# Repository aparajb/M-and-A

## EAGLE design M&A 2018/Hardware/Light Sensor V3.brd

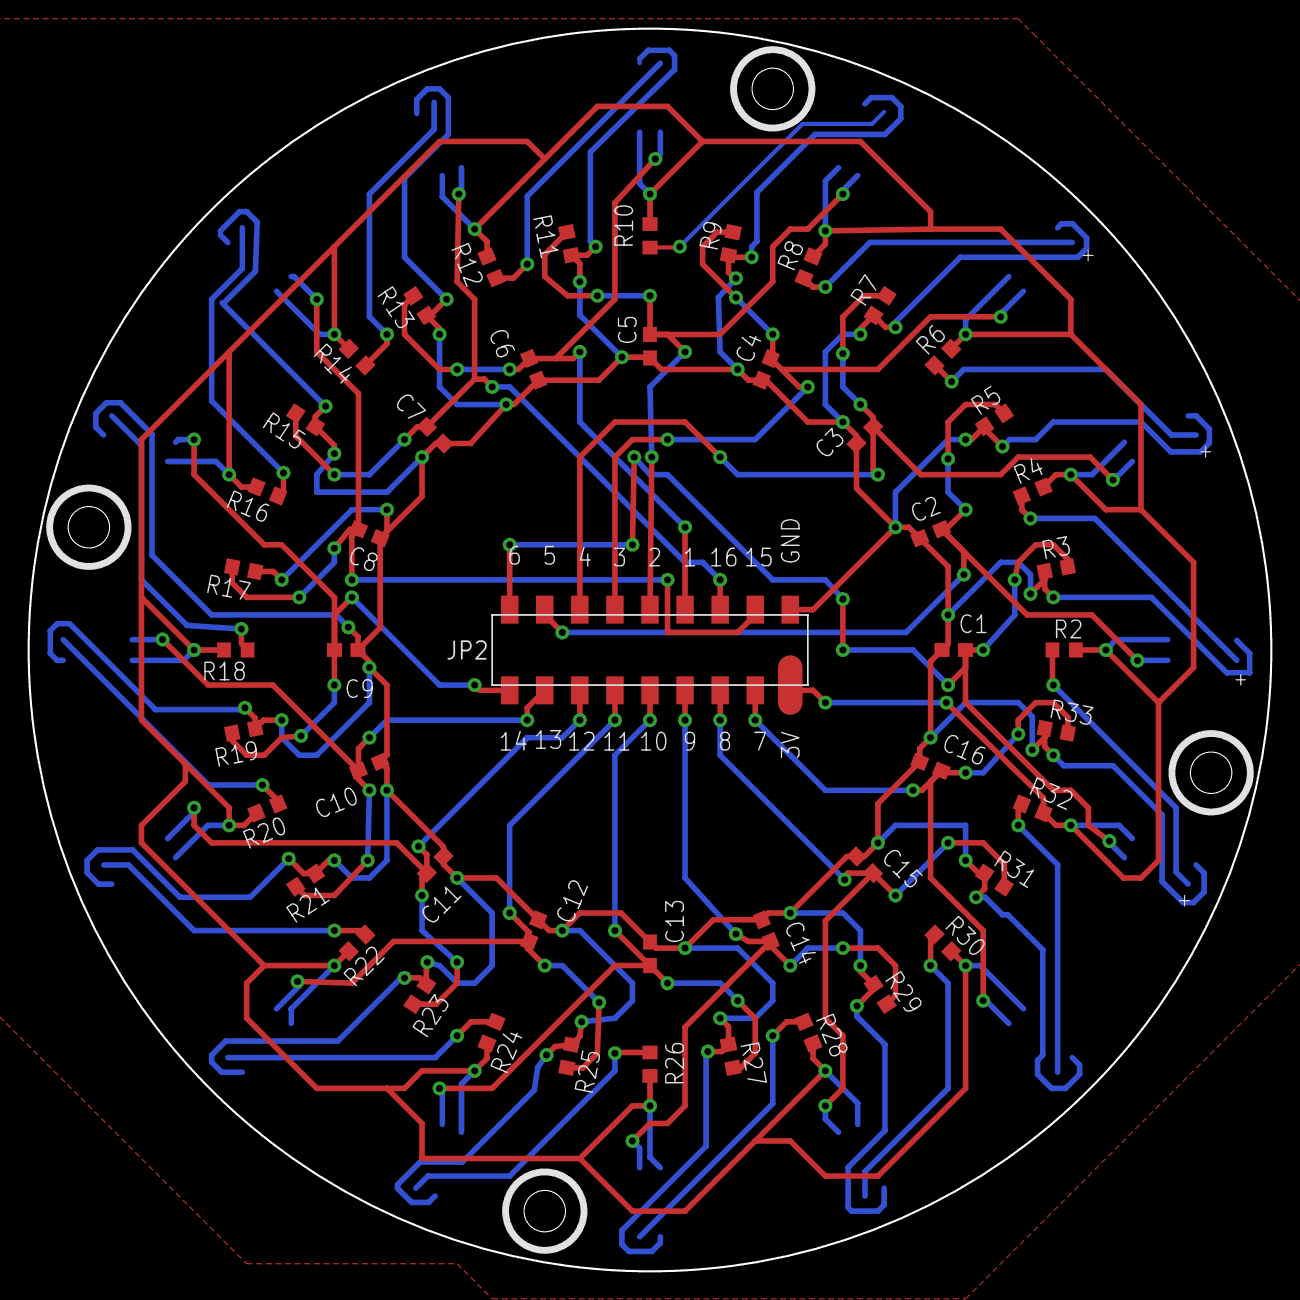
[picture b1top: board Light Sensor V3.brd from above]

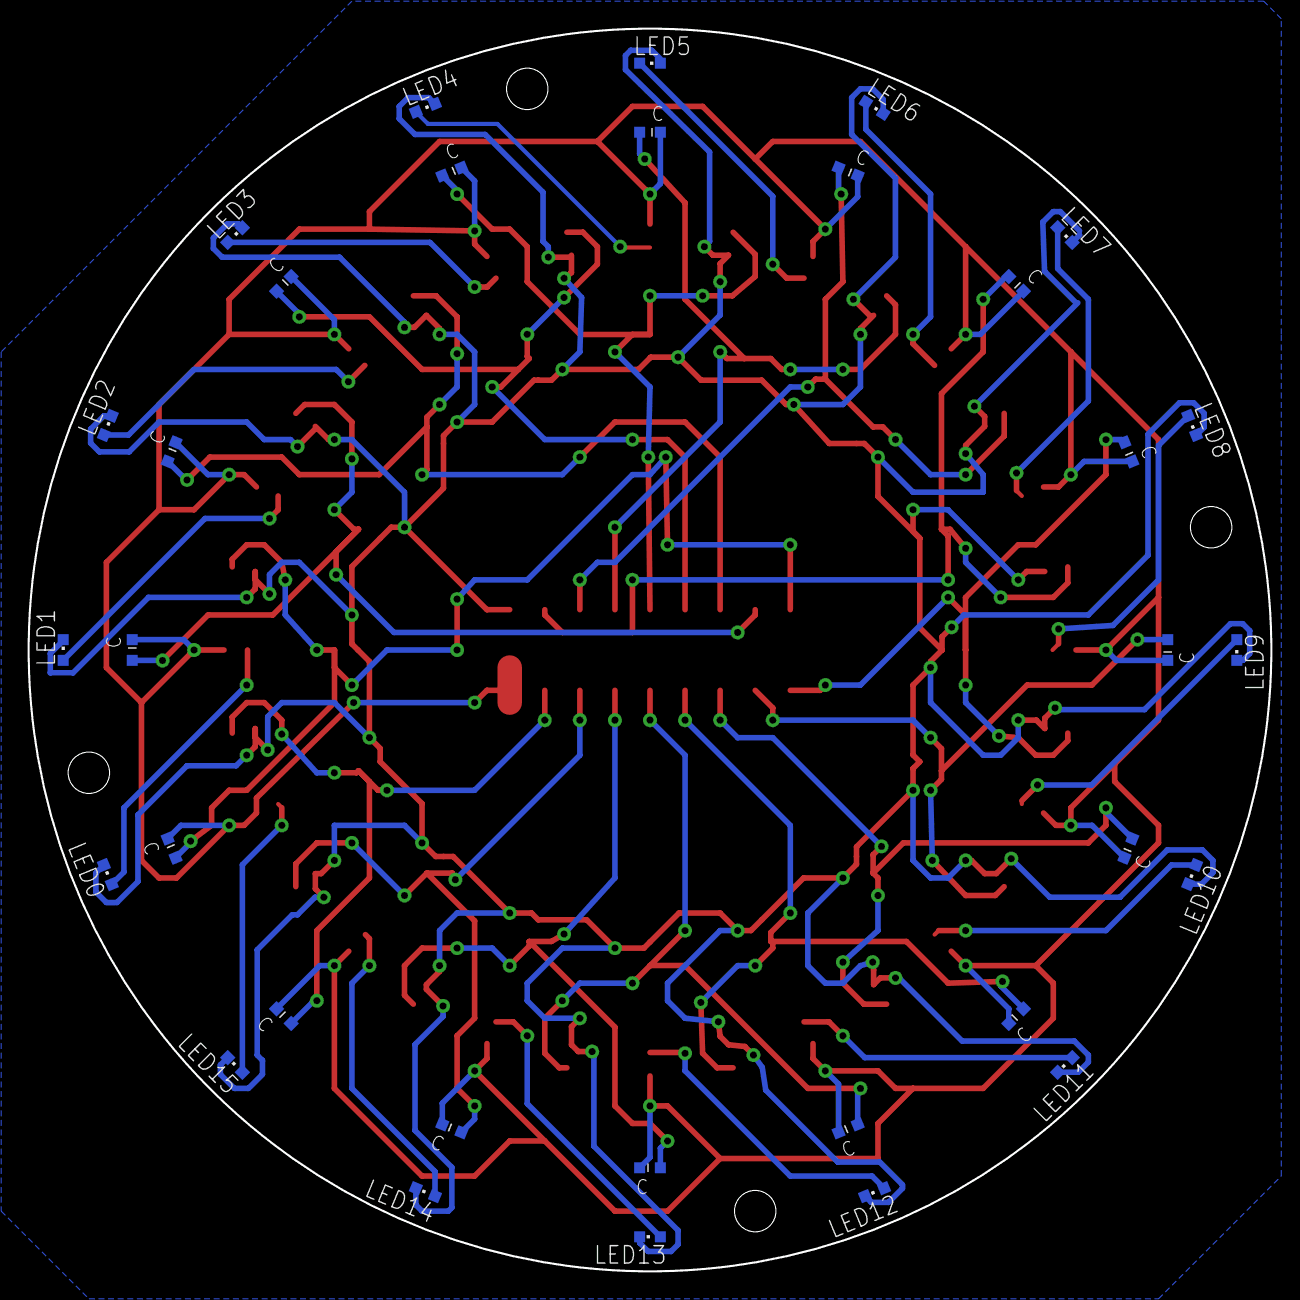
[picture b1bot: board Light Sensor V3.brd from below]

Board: 2 copper layers, 90.0 x 90.0 mm, 81 parts (32 on the bottom side), 34 nets.

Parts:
C1, C2, C3, C4, C5, C6, C7, C8, C9, C10, C11, C12, C13, C14, C15, C16: 0.1uF; C0603
JP2: 2X09_SMT
LED0, LED1, LED2, LED3, LED4, LED5, LED6, LED7, LED8, LED9, LED10, LED11, LED12, LED13, LED14, LED15: CHIPLED_0603
LS0, LS1, LS2, LS3, LS4, LS5, LS6, LS7, LS8, LS9, LS10, LS11, LS12, LS13, LS14, LS15: ALS; SMD
R2, R4, R6, R8, R10, R12, R14, R16, R18, R20, R22, R24, R26, R28, R30, R32: 100; R0603
R3, R5, R7, R9, R11, R13, R15, R17, R19, R21, R23, R25, R27, R29, R31, R33: 33K; R0603

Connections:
+3V3: JP2.17, LS0.C, LS1.C, LS2.C, LS3.C, LS4.C, LS5.C, LS6.C, LS7.C, LS8.C, LS9.C, LS10.C, LS11.C, LS12.C, LS13.C, LS14.C, LS15.C, R2.2, R4.2, R6.2, R8.2, R10.2, R12.2, R14.2, R16.2, R18.2, R20.2, R22.2, R24.2, R26.2, R28.2, R30.2, R32.2
GND: C1.1, C2.1, C3.1, C4.1, C5.1, C6.1, C7.1, C8.1, C9.1, C10.1, C11.1, C12.1, C13.1, C14.1, C15.1, C16.1, JP2.18, LED0.C, LED1.C, LED2.C, LED3.C, LED4.C, LED5.C, LED6.C, LED7.C, LED8.C, LED9.C, LED10.C, LED11.C, LED12.C, LED13.C, LED14.C, LED15.C, R3.1, R5.1, R7.1, R9.1, R11.1, R13.1, R15.1, R17.1, R19.1, R21.1, R23.1, R25.1, R27.1, R29.1, R31.1, R33.1
LS0: C1.2, JP2.2, LS0.E, R3.2
LS1: C2.2, JP2.4, LS1.E, R5.2
LS2: C3.2, JP2.6, LS2.E, R7.2
LS3: C4.2, JP2.8, LS3.E, R9.2
LS4: C5.2, JP2.10, LS4.E, R11.2
LS5: C6.2, JP2.12, LS5.E, R13.2
LS6: C7.2, JP2.14, LS6.E, R15.2
LS7: C8.2, JP2.16, LS7.E, R17.2
LS8: C9.2, JP2.1, LS8.E, R19.2
LS9: C10.2, JP2.3, LS9.E, R21.2
LS10: C11.2, JP2.5, LS10.E, R23.2
LS11: C12.2, JP2.7, LS11.E, R25.2
LS12: C13.2, JP2.9, LS12.E, R27.2
LS13: C14.2, JP2.11, LS13.E, R29.2
LS14: C15.2, JP2.13, LS14.E, R31.2
LS15: C16.2, JP2.15, LS15.E, R33.2
unnamed: LED0.A, R2.1
unnamed: LED1.A, R4.1
unnamed: LED2.A, R6.1
unnamed: LED3.A, R8.1
unnamed: LED4.A, R10.1
unnamed: LED5.A, R12.1
unnamed: LED6.A, R14.1
unnamed: LED7.A, R16.1
unnamed: LED8.A, R18.1
unnamed: LED9.A, R20.1
unnamed: LED10.A, R22.1
unnamed: LED11.A, R24.1
unnamed: LED12.A, R26.1
unnamed: LED13.A, R28.1
unnamed: LED14.A, R30.1
unnamed: LED15.A, R32.1

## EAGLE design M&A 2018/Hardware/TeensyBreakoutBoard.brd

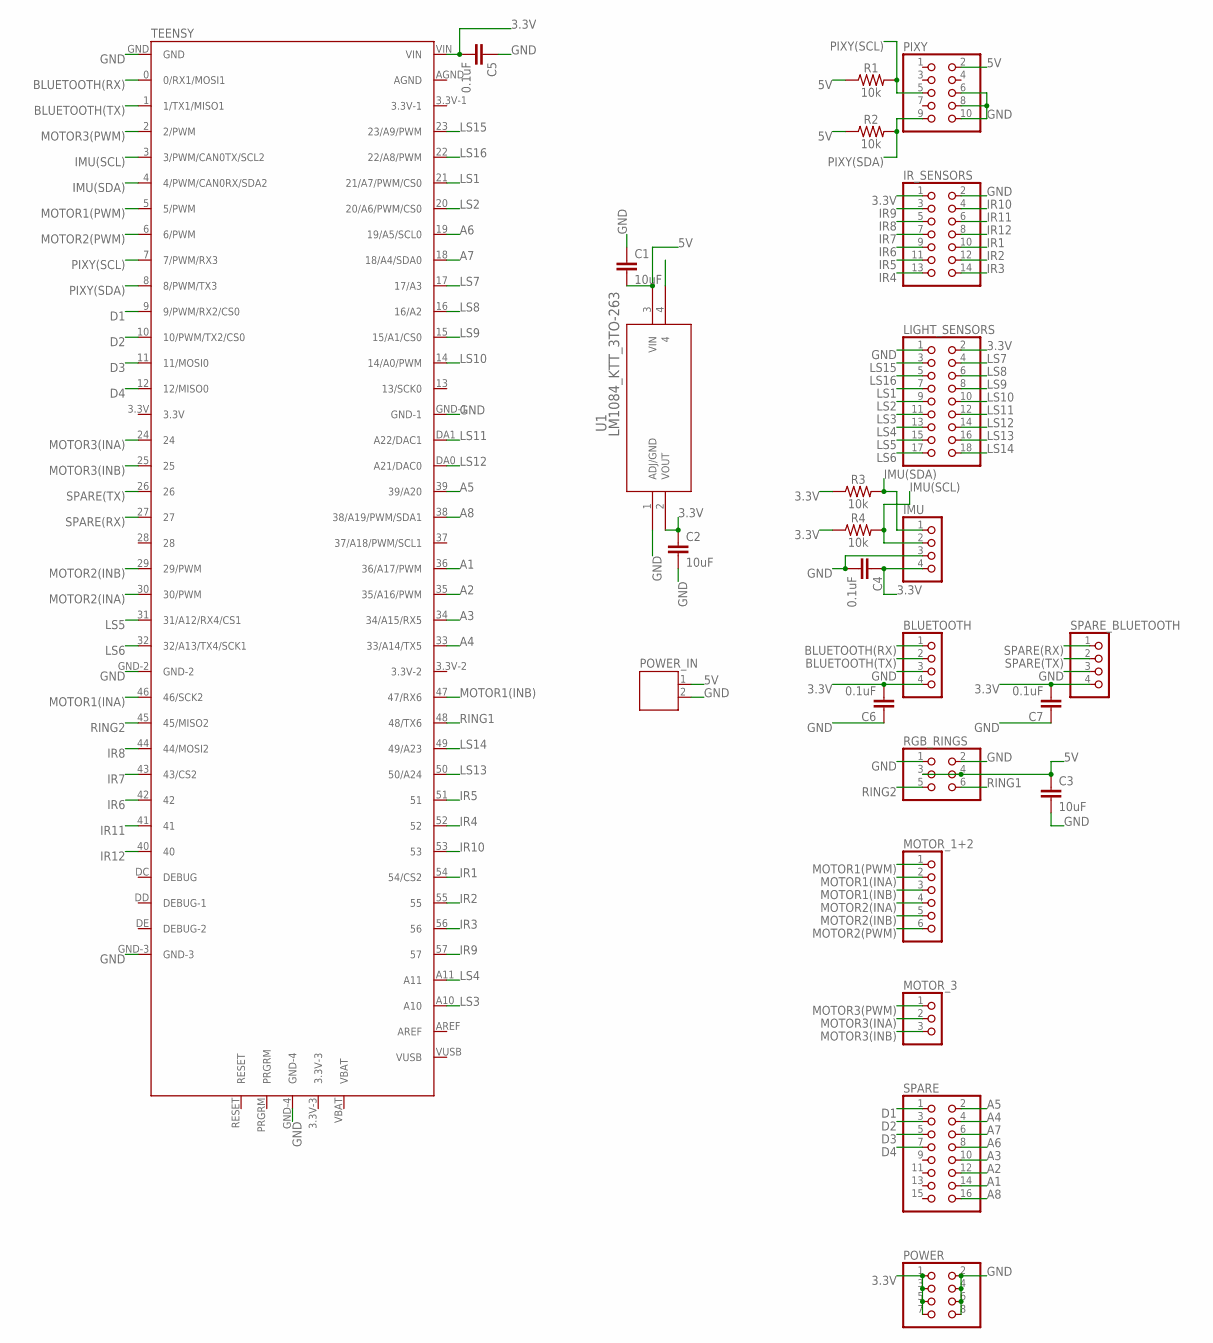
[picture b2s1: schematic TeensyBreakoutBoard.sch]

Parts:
BLUETOOTH: PINHD-1X4; 1X04
C1, C2, C3: 10uF; 0805
C4, C5, C6, C7: 0.1uF; 0603
IMU: PINHD-1X4; 1X04
IR_SENSORS: PINHD-2X7; 2X07
LIGHT_SENSORS: PINHD-2X9; 2X09
MOTOR_1+2: PINHD-1X6; 1X06
MOTOR_3: PINHD-1X3; 1X03
PIXY: PINHD-2X5; 2X05
POWER: PINHD-2X4; 2X04
POWER_IN: JST-PH2
R1, R2, R3, R4: 10k; 0603
RGB_RINGS: PINHD-2X3; 2X03
SPARE: PINHD-2X8; 2X08
SPARE_BLUETOOTH: PINHD-1X4; 1X04
TEENSY: TEENSY-3.5
U1: LM1084_KTT_3TO-263; TS3B

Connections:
3.3V: BLUETOOTH.4, C2.1, C4.1, C5.2, C6.2, C7.2, IMU.4, IR_SENSORS.1, LIGHT_SENSORS.2, POWER.1, POWER.3, POWER.5, POWER.7, R3.1, R4.1, SPARE_BLUETOOTH.4, TEENSY.VIN, U1.2 (VOUT)
5V: C1.2, C3.1, PIXY.2, POWER_IN.1, R1.1, R2.1, RGB_RINGS.3, RGB_RINGS.4, U1.3 (VIN)
A1: SPARE.14, TEENSY.36 (36/A17/PWM)
A2: SPARE.12, TEENSY.35 (35/A16/PWM)
A3: SPARE.10, TEENSY.34 (34/A15/RX5)
A4: SPARE.4, TEENSY.33 (33/A14/TX5)
A5: SPARE.2, TEENSY.39 (39/A20)
A6: SPARE.8, TEENSY.19 (19/A5/SCL0)
A7: SPARE.6, TEENSY.18 (18/A4/SDA0)
A8: SPARE.16, TEENSY.38 (38/A19/PWM/SDA1)
BLUETOOTH(RX): BLUETOOTH.1, TEENSY.0 (0/RX1/MOSI1)
BLUETOOTH(TX): BLUETOOTH.2, TEENSY.1 (1/TX1/MISO1)
D1: SPARE.1, TEENSY.9 (9/PWM/RX2/CS0)
D2: SPARE.3, TEENSY.10 (10/PWM/TX2/CS0)
D3: SPARE.5, TEENSY.11 (11/MOSI0)
D4: SPARE.7, TEENSY.12 (12/MISO0)
GND: BLUETOOTH.3, C1.1, C2.2, C3.2, C4.2, C5.1, C6.1, C7.1, IMU.3, IR_SENSORS.2, LIGHT_SENSORS.1, PIXY.6, PIXY.8, PIXY.10, POWER.2, POWER.4, POWER.6, POWER.8, POWER_IN.2, RGB_RINGS.1, RGB_RINGS.2, SPARE_BLUETOOTH.3, TEENSY.GND, TEENSY.GND-1, TEENSY.GND-2, TEENSY.GND-3, TEENSY.GND-4, U1.1 (ADJ/GND)
IMU(SCL): IMU.2, R4.2, TEENSY.3 (3/PWM/CAN0TX/SCL2)
IMU(SDA): IMU.1, R3.2, TEENSY.4 (4/PWM/CAN0RX/SDA2)
IR1: IR_SENSORS.10, TEENSY.54 (54/CS2)
IR2: IR_SENSORS.12, TEENSY.55
IR3: IR_SENSORS.14, TEENSY.56
IR4: IR_SENSORS.13, TEENSY.52
IR5: IR_SENSORS.11, TEENSY.51
IR6: IR_SENSORS.9, TEENSY.42
IR7: IR_SENSORS.7, TEENSY.43 (43/CS2)
IR8: IR_SENSORS.5, TEENSY.44 (44/MOSI2)
IR9: IR_SENSORS.3, TEENSY.57
IR10: IR_SENSORS.4, TEENSY.53
IR11: IR_SENSORS.6, TEENSY.41
IR12: IR_SENSORS.8, TEENSY.40
LS1: LIGHT_SENSORS.7, TEENSY.21 (21/A7/PWM/CS0)
LS2: LIGHT_SENSORS.9, TEENSY.20 (20/A6/PWM/CS0)
LS3: LIGHT_SENSORS.11, TEENSY.A10
LS4: LIGHT_SENSORS.13, TEENSY.A11
LS5: LIGHT_SENSORS.15, TEENSY.31 (31/A12/RX4/CS1)
LS6: LIGHT_SENSORS.17, TEENSY.32 (32/A13/TX4/SCK1)
LS7: LIGHT_SENSORS.4, TEENSY.17 (17/A3)
LS8: LIGHT_SENSORS.6, TEENSY.16 (16/A2)
LS9: LIGHT_SENSORS.8, TEENSY.15 (15/A1/CS0)
LS10: LIGHT_SENSORS.10, TEENSY.14 (14/A0/PWM)
LS11: LIGHT_SENSORS.12, TEENSY.DA1 (A22/DAC1)
LS12: LIGHT_SENSORS.14, TEENSY.DA0 (A21/DAC0)
LS13: LIGHT_SENSORS.16, TEENSY.50 (50/A24)
LS14: LIGHT_SENSORS.18, TEENSY.49 (49/A23)
LS15: LIGHT_SENSORS.3, TEENSY.23 (23/A9/PWM)
LS16: LIGHT_SENSORS.5, TEENSY.22 (22/A8/PWM)
MOTOR1(INA): MOTOR_1+2.2, TEENSY.46 (46/SCK2)
MOTOR1(INB): MOTOR_1+2.3, TEENSY.47 (47/RX6)
MOTOR1(PWM): MOTOR_1+2.1, TEENSY.5 (5/PWM)
MOTOR2(INA): MOTOR_1+2.4, TEENSY.30 (30/PWM)
MOTOR2(INB): MOTOR_1+2.5, TEENSY.29 (29/PWM)
MOTOR2(PWM): MOTOR_1+2.6, TEENSY.6 (6/PWM)
MOTOR3(INA): MOTOR_3.2, TEENSY.24
MOTOR3(INB): MOTOR_3.3, TEENSY.25
MOTOR3(PWM): MOTOR_3.1, TEENSY.2 (2/PWM)
PIXY(SCL): PIXY.5, R1.2, TEENSY.7 (7/PWM/RX3)
PIXY(SDA): PIXY.9, R2.2, TEENSY.8 (8/PWM/TX3)
RING1: RGB_RINGS.6, TEENSY.48 (48/TX6)
RING2: RGB_RINGS.5, TEENSY.45 (45/MISO2)
SPARE(RX): SPARE_BLUETOOTH.1, TEENSY.27
SPARE(TX): SPARE_BLUETOOTH.2, TEENSY.26

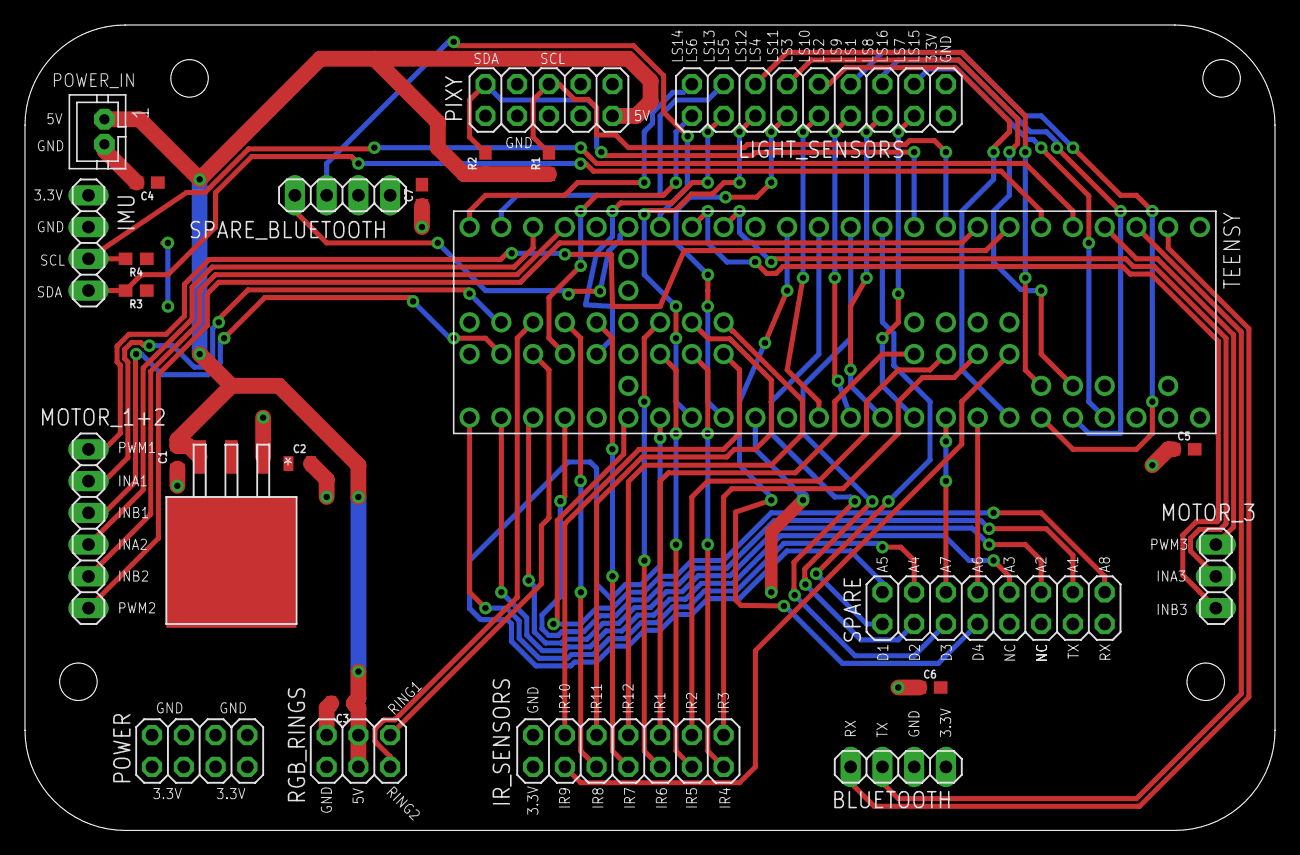
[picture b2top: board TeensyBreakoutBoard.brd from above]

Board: 2 copper layers, 100.0 x 64.4 mm, 25 parts (0 on the bottom side), 62 nets.

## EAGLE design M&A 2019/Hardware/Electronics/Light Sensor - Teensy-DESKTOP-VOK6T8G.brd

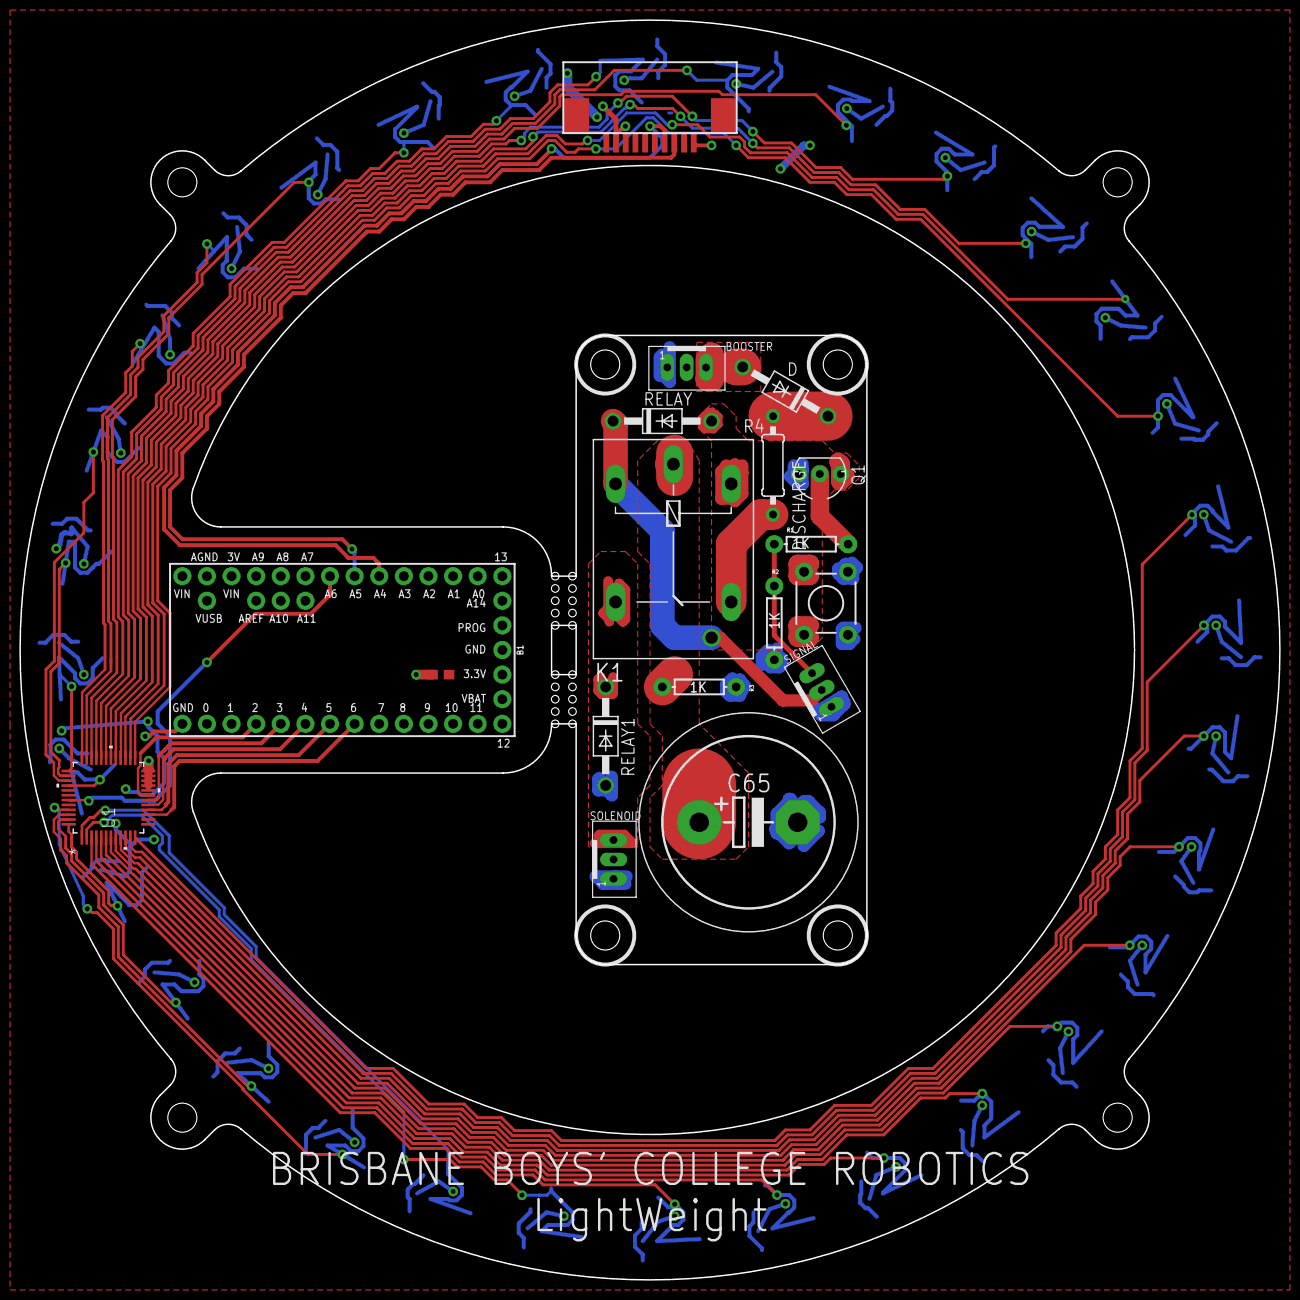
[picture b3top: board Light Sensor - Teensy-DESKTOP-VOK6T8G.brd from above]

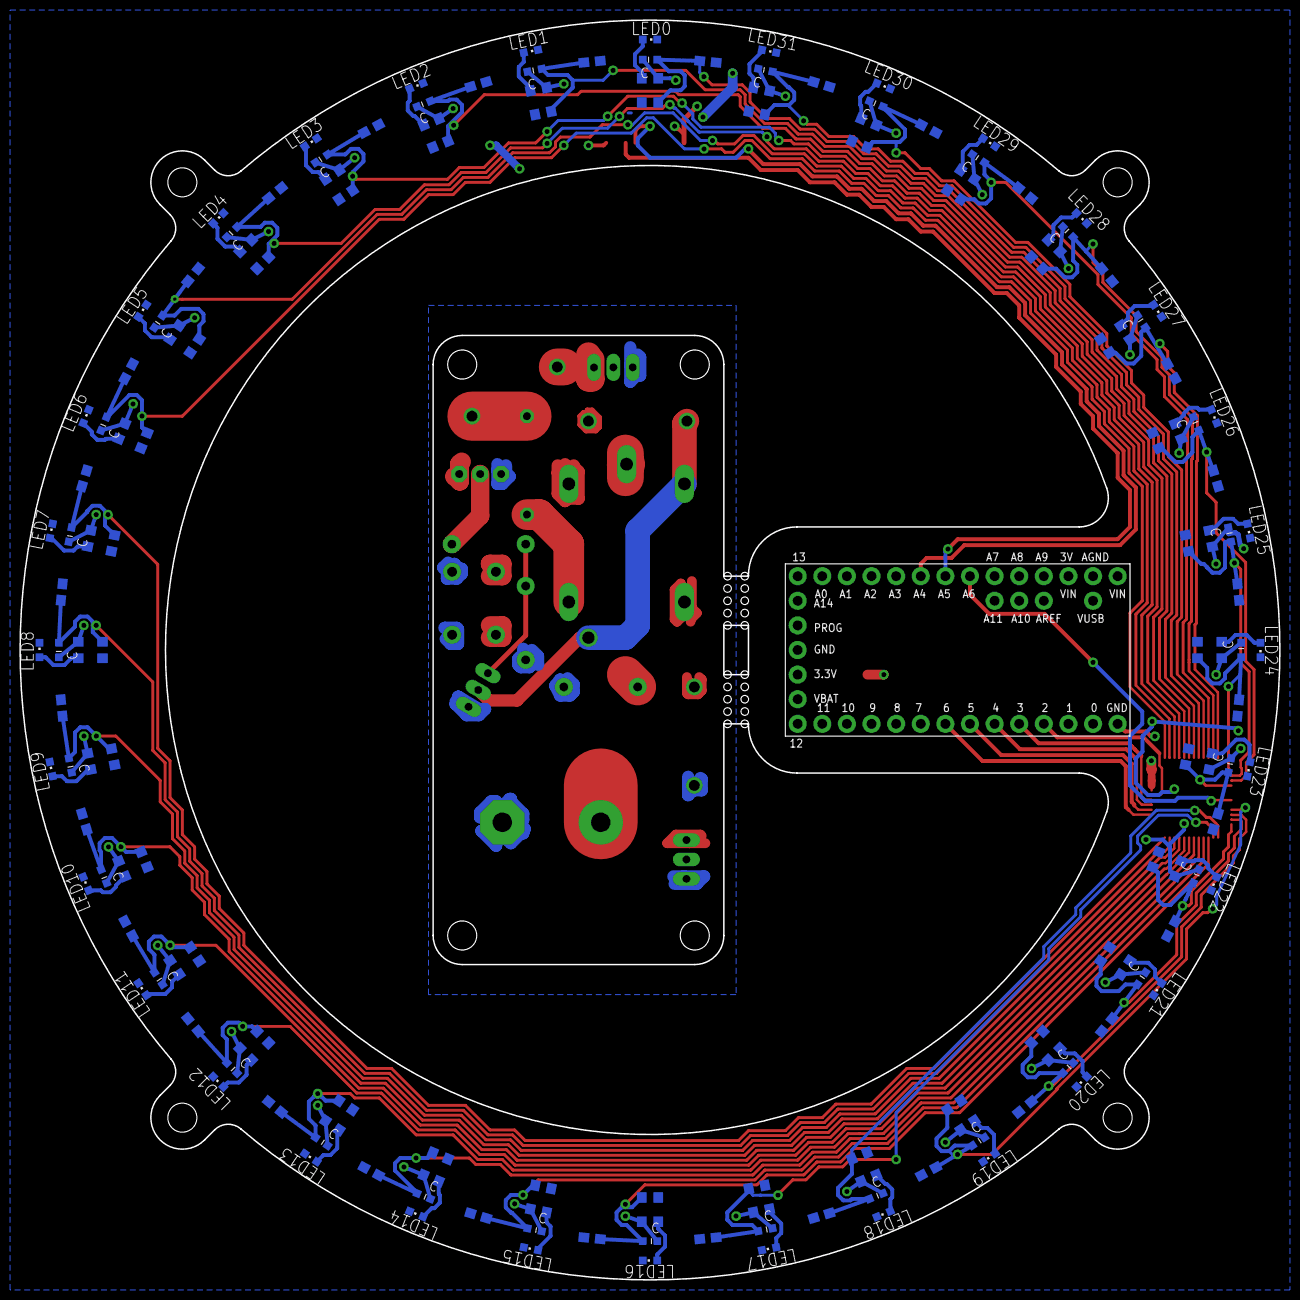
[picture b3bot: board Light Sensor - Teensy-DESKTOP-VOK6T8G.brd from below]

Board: 2 copper layers, 130.0 x 130.0 mm, 178 parts (160 on the bottom side), 83 nets.

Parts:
B1: TEENSY-3.1SILK; TEENSY-3.1
BOOSTER: JST-PH_3-PIN_HEADER; JST_B3B-PH_HEADER
C1, C2, C3, C4, C5, C6, C7, C8, C9, C10, C11, C12, C13, C14, C15, C16, C17, C18, C19, C20, C21, C22, C23, C24, C25, C26, C27, C28, C29, C30, C31, C32: 0.1uF; C0603
C33: 0.1uF; 0603
C65: 3300uF; EB22,5D
D: 1N4004; DO41-10
DISCHARGE: TACTILE-PTH
K1: G5LE
LED0, LED1, LED2, LED3, LED4, LED5, LED6, LED7, LED8, LED9, LED10, LED11, LED12, LED13, LED14, LED15, LED16, LED17, LED18, LED19, LED20, LED21, LED22, LED23, LED24, LED25, LED26, LED27, LED28, LED29, LED30, LED31: CHIPLED_0603
LS0, LS1, LS2, LS3, LS4, LS5, LS6, LS7, LS8, LS9, LS10, LS11, LS12, LS13, LS14, LS15, LS16, LS17, LS18, LS19, LS20, LS21, LS22, LS23, LS24, LS25, LS26, LS27, LS28, LS29, LS30, LS31: ALS; SMD
Q1: FQN1N50CI; TO92-INLINE
R1, R2, R3: 1K; AXIAL-0.3
R4: 50ohm; 0207/10
RELAY, RELAY1: 1N4004; DO41-10
RL1, RL2, RL3, RL4, RL5, RL6, RL7, RL8, RL9, RL10, RL11, RL12, RL13, RL14, RL15, RL16, RL17, RL18, RL19, RL20, RL21, RL22, RL23, RL24, RL25, RL26, RL27, RL28, RL29, RL30, RL31, RL32: 100; R0603
RS1, RS2, RS3, RS4, RS5, RS6, RS7, RS8, RS9, RS10, RS11, RS12, RS13, RS14, RS15, RS16, RS17, RS18, RS19, RS20, RS21, RS22, RS23, RS24, RS25, RS26, RS27, RS28, RS29, RS30, RS31, RS32: 33K; R0603
SIGNAL: JST-PH_3-PIN_HEADER; JST_B3B-PH_HEADER
SOLENOID: JST-PH_3-PIN_HEADER; JST_B3B-PH_HEADER
U1: ADG732BSUZ-REEL; SU_48
U$1: FPC10

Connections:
+3V3: B1.3.3V, C33.2, LS0.C, LS1.C, LS2.C, LS3.C, LS4.C, LS5.C, LS6.C, LS7.C, LS8.C, LS9.C, LS10.C, LS11.C, LS12.C, LS13.C, LS14.C, LS15.C, LS16.C, LS17.C, LS18.C, LS19.C, LS20.C, LS21.C, LS22.C, LS23.C, LS24.C, LS25.C, LS26.C, LS27.C, LS28.C, LS29.C, LS30.C, LS31.C, RL1.2, RL2.2, RL3.2, RL4.2, RL5.2, RL6.2, RL7.2, RL8.2, RL9.2, RL10.2, RL11.2, RL12.2, RL13.2, RL14.2, RL15.2, RL16.2, RL17.2, RL18.2, RL19.2, RL20.2, RL21.2, RL22.2, RL23.2, RL24.2, RL25.2, RL26.2, RL27.2, RL28.2, RL29.2, RL30.2, RL31.2, RL32.2, U1.13, U1.14, U$1.2, U$1.10
+12V: K1.1, RELAY.C, SIGNAL.P2
CHARGE: C65.+, K1.P, R3.P$2
CONTROL1: B1.2, U1.19
CONTROL2: B1.3, U1.18
CONTROL3: B1.4, U1.17
CONTROL4: B1.5, U1.16
CONTROL5: B1.6, U1.15
GND: B1.GND, B1.GND1, BOOSTER.P1, C1.1, C2.1, C3.1, C4.1, C5.1, C6.1, C7.1, C8.1, C9.1, C10.1, C11.1, C12.1, C13.1, C14.1, C15.1, C16.1, C17.1, C18.1, C19.1, C20.1, C21.1, C22.1, C23.1, C24.1, C25.1, C26.1, C27.1, C28.1, C29.1, C30.1, C31.1, C32.1, C33.1, C65.-, DISCHARGE.1, DISCHARGE.2, LED0.C, LED1.C, LED2.C, LED3.C, LED4.C, LED5.C, LED6.C, LED7.C, LED8.C, LED9.C, LED10.C, LED11.C, LED12.C, LED13.C, LED14.C, LED15.C, LED16.C, LED17.C, LED18.C, LED19.C, LED20.C, LED21.C, LED22.C, LED23.C, LED24.C, LED25.C, LED26.C, LED27.C, LED28.C, LED29.C, LED30.C, LED31.C, Q1.3, R2.P$1, R3.P$1, RELAY1.A, RS1.1, RS2.1, RS3.1, RS4.1, RS5.1, RS6.1, RS7.1, RS8.1, RS9.1, RS10.1, RS11.1, RS12.1, RS13.1, RS14.1, RS15.1, RS16.1, RS17.1, RS18.1, RS19.1, RS20.1, RS21.1, RS22.1, RS23.1, RS24.1, RS25.1, RS26.1, RS27.1, RS28.1, RS29.1, RS30.1, RS31.1, RS32.1, SIGNAL.P1, SOLENOID.P1, U1.20, U1.21, U1.22, U1.23, U1.24, U$1.1, U$1.9
LS0: C1.2, LS0.E, RS1.2, U1.31
LS1: C2.2, LS1.E, RS2.2, U1.30
LS2: C3.2, LS2.E, RS3.2, U1.29
LS3: C4.2, LS3.E, RS4.2, U1.28
LS4: C5.2, LS4.E, RS5.2, U1.27
LS5: C6.2, LS5.E, RS6.2, U1.26
LS6: C7.2, LS6.E, RS7.2, U1.25
LS7: C8.2, LS7.E, RS8.2, U1.12
LS8: C9.2, LS8.E, RS9.2, U1.11
LS9: C10.2, LS9.E, RS10.2, U1.10
LS10: C11.2, LS10.E, RS11.2, U1.9
LS11: C12.2, LS11.E, RS12.2, U1.8
LS12: C13.2, LS12.E, RS13.2, U1.7
LS13: C14.2, LS13.E, RS14.2, U1.6
LS14: C15.2, LS14.E, RS15.2, U1.5
LS15: C16.2, LS15.E, RS16.2, U1.4
LS16: C17.2, LS16.E, RS17.2, U1.3
LS17: C18.2, LS17.E, RS18.2, U1.2
LS18: C19.2, LS18.E, RS19.2, U1.1
LS19: C20.2, LS19.E, RS20.2, U1.45
LS20: C21.2, LS20.E, RS21.2, U1.46
LS21: C22.2, LS21.E, RS22.2, U1.47
LS22: C23.2, LS22.E, RS23.2, U1.48
LS23: C24.2, LS23.E, RS24.2, U1.40
LS24: C25.2, LS24.E, RS25.2, U1.37
LS25: C26.2, LS25.E, RS26.2, U1.38
LS26: C27.2, LS26.E, RS27.2, U1.39
LS27: C28.2, LS27.E, RS28.2, U1.36
LS28: C29.2, LS28.E, RS29.2, U1.35
LS29: C30.2, LS29.E, RS30.2, U1.34
LS30: C31.2, LS30.E, RS31.2, U1.33
LS31: C32.2, LS31.E, RS32.2, U1.32
unnamed: LED0.A, RL1.1
unnamed: LED1.A, RL2.1
unnamed: LED2.A, RL3.1
unnamed: LED3.A, RL4.1
unnamed: LED4.A, RL5.1
unnamed: LED5.A, RL6.1
unnamed: LED6.A, RL7.1
unnamed: LED7.A, RL8.1
unnamed: LED8.A, RL9.1
unnamed: LED9.A, RL10.1
unnamed: LED10.A, RL11.1
unnamed: LED11.A, RL12.1
unnamed: LED12.A, RL13.1
unnamed: LED13.A, RL14.1
unnamed: LED14.A, RL15.1
unnamed: LED15.A, RL16.1
unnamed: LED16.A, RL17.1
unnamed: LED17.A, RL18.1
unnamed: LED18.A, RL19.1
unnamed: LED19.A, RL20.1
unnamed: LED20.A, RL21.1
unnamed: LED21.A, RL22.1
unnamed: LED22.A, RL23.1
unnamed: LED23.A, RL24.1
unnamed: LED24.A, RL25.1
unnamed: LED25.A, RL26.1
unnamed: LED26.A, RL27.1
unnamed: LED27.A, RL28.1
unnamed: LED28.A, RL29.1
unnamed: LED29.A, RL30.1
unnamed: LED30.A, RL31.1
unnamed: LED31.A, RL32.1
unnamed: Q1.2, R1.P$2
unnamed: BOOSTER.P3, D.A
unnamed: D.C, R4.2
OUT: K1.S, RELAY1.C, SOLENOID.P3
OUTPUT: B1.20, U1.43
RELAY: DISCHARGE.3, DISCHARGE.4, K1.2, Q1.1, RELAY.A
SCL: B1.19, U$1.3
SDA: B1.18, U$1.4
SIGNAL: R1.P$1, R2.P$2, SIGNAL.P3
VCC: K1.O, R4.1

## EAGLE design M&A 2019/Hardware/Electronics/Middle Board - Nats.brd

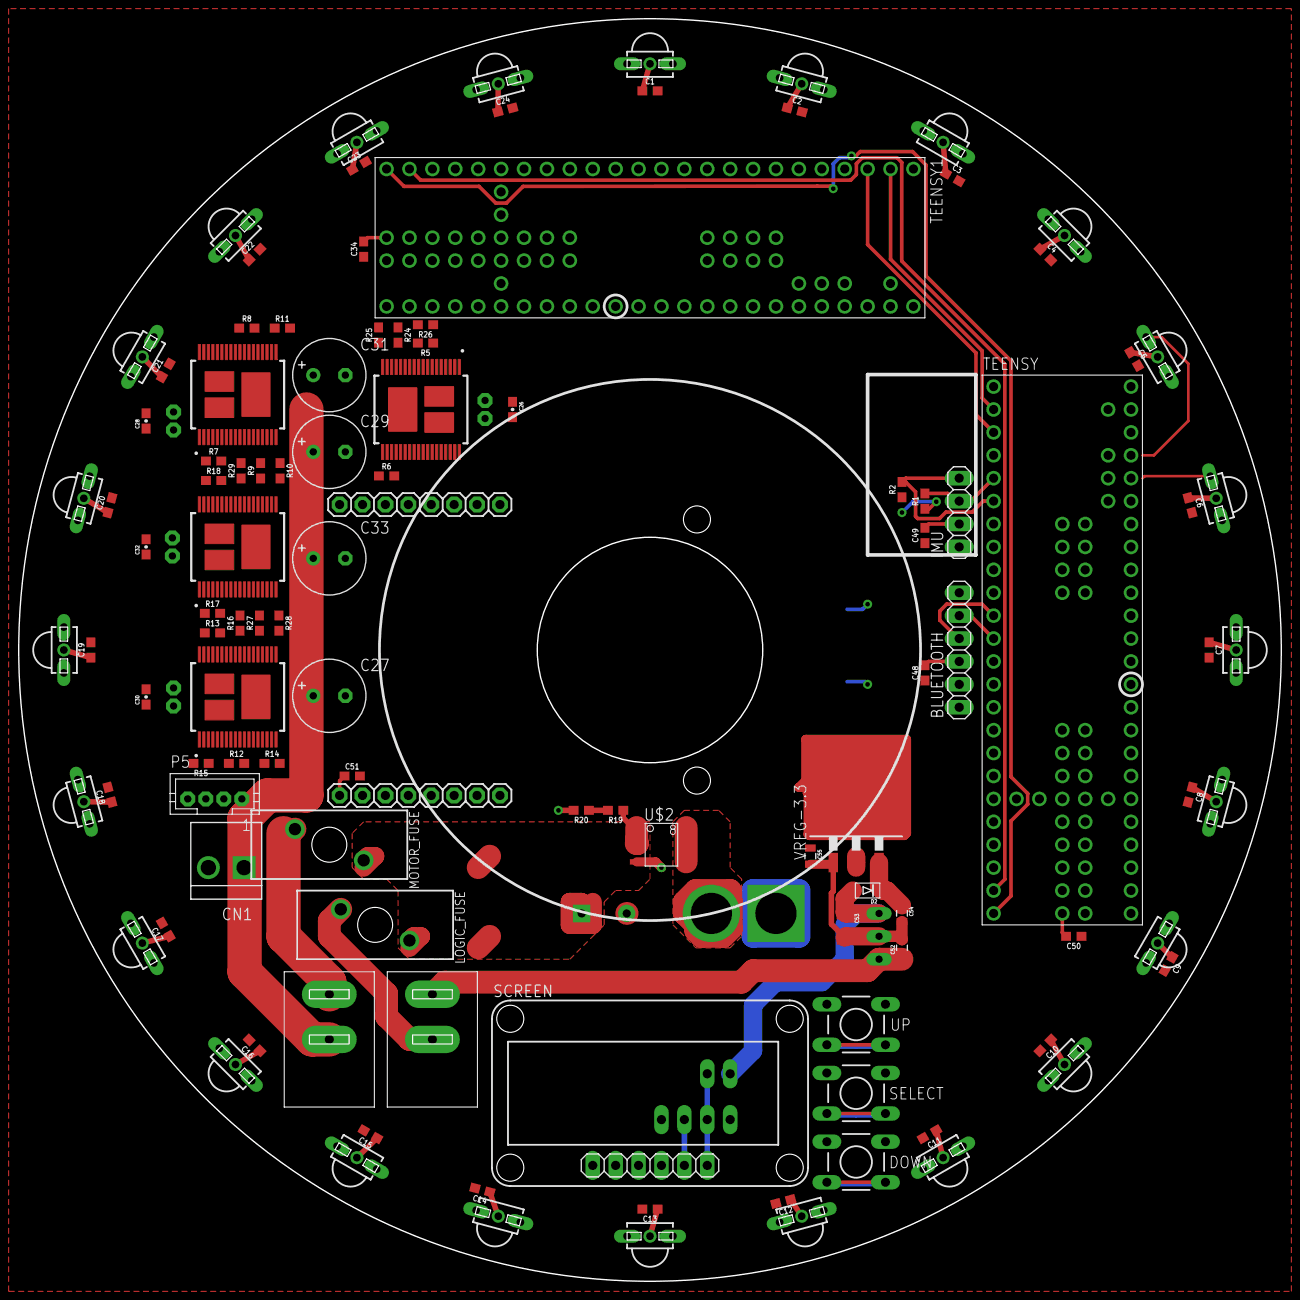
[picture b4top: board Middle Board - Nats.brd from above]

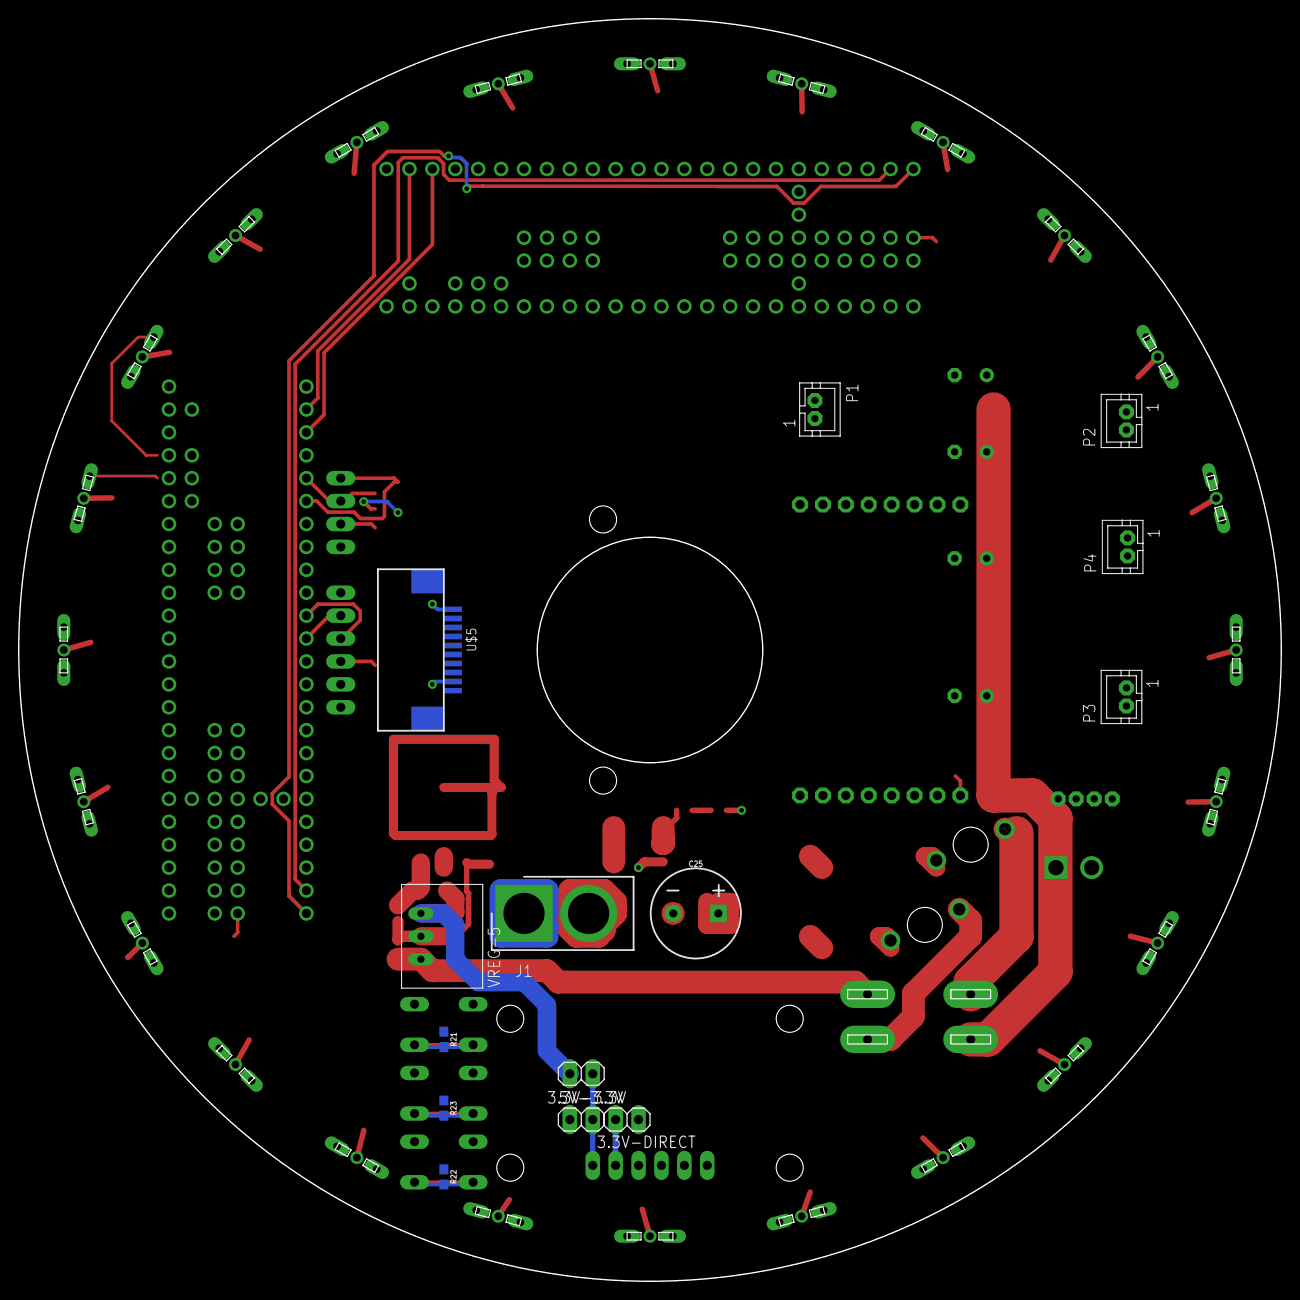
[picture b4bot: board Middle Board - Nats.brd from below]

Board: 2 copper layers, 140.0 x 140.0 mm, 125 parts (14 on the bottom side), 56 nets.

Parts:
3.3V-3.3V, 3.3V-DIRECT, 5V-3.3V: 1X02
BLUETOOTH: 1X06
C1, C2, C3, C4, C5, C6, C7, C8, C9, C10, C11, C12, C13, C14, C15, C16, C17, C18, C19, C20, C21, C22, C23, C24, C34, C48, C49, C50, C51: 0.1uF; 0603
C25: 1mF; CPOL-RADIAL-5MM-10MM
C26, C28, C30, C32: 0.1UF_CAPACITOR_SMD; SPARKFUN-CAPACITORS_0603-CAP
C27, C29, C31, C33: 470uF; E3,5-8
C52, C54, C55: 10uF; SPARKFUN-CAPACITORS_0805
C53: 22uF; SPARKFUN-CAPACITORS_1206
CN1: B2P-VH
D2: ADAFRUIT_SOD-123FL
DOWN: DTS-6
IMU: 1X04
J1: PRT-10474; SHDR2W320P716_1X2_1574X813X158
LOGIC_FUSE: FUSE_MINI_BLADE; SL-1538
MOTOR_1, MOTOR_2, MOTOR_3, MOTOR_5: SOP50P1030X247-36N
MOTOR_FUSE: FUSE_MINI_BLADE; SL-1538
OPEN-MV: OPENMV3
P1, P2, P3, P4: JST-PH2
P5: JST-PH4
R1, R2, R21, R22, R23: 10k; 0603
R5, R6, R7, R8, R9, R10, R12, R13, R14, R15, R17, R18, R24, R25, R27, R28: 1k; 0603
R11, R16, R26, R29: 4.7k; 0603
R19: 35.7kOhm; 0603
R20: 10.2kOhm; 0603
SCREEN: 1X06
SELECT: DTS-6
TEENSY, TEENSY1: TEENSY-3.5
TSSP1, TSSP2, TSSP3, TSSP4, TSSP5, TSSP6, TSSP7, TSSP8, TSSP9, TSSP10, TSSP11, TSSP12, TSSP13, TSSP14, TSSP15, TSSP16, TSSP17, TSSP18, TSSP19, TSSP20, TSSP21, TSSP22, TSSP23, TSSP24: TSSP58038; MINICAST
U$1, U$3: MINI_SWITCH; SWITCH
U$2: SI4143DY; SO-8
U$5: FPC10
UP: DTS-6
VREG-3.3: LINEAR_LM340S-05; LINEAR_TO263-3
VREG-5: V78-2000-SWITCHING-REGULATOR_V78-2000

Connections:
3.3V: 3.3V-3.3V.1, 3.3V-DIRECT.1, BLUETOOTH.2, C1.2, C2.2, C3.2, C4.2, C5.2, C6.2, C7.2, C8.2, C9.2, C10.2, C11.2, C12.2, C13.2, C14.2, C15.2, C16.2, C17.2, C18.2, C19.2, C20.2, C21.2, C22.2, C23.2, C24.2, C34.1, C48.1, C49.1, C50.1, C51.2, C55.1, DOWN.1, DOWN.2, IMU.1, OPEN-MV.27, R1.1, R2.1, SELECT.1, SELECT.2, TEENSY.3.3V, TEENSY.3.3V-1, TEENSY.3.3V-2, TEENSY.3.3V-3, TEENSY1.3.3V-1, TEENSY1.3.3V-2, TEENSY1.3.3V-3, TSSP1.1, TSSP2.1, TSSP3.1, TSSP4.1, TSSP5.1, TSSP6.1, TSSP7.1, TSSP8.1, TSSP9.1, TSSP10.1, TSSP11.1, TSSP12.1, TSSP13.1, TSSP14.1, TSSP15.1, TSSP16.1, TSSP17.1, TSSP18.1, TSSP19.1, TSSP20.1, TSSP21.1, TSSP22.1, TSSP23.1, TSSP24.1, U$5.1, U$5.9, UP.1, UP.2, VREG-3.3.2, VREG-3.3.TAB
5V: 5V-3.3V.1, C53.1, D2.A, R11.2, R16.2, R26.2, R29.2, VREG-5.3
12V: C27.+, C29.+, C31.+, C33.+, CN1.1, MOTOR_1.13, MOTOR_1.24, MOTOR_1.SLUG1, MOTOR_2.13, MOTOR_2.24, MOTOR_2.SLUG1, MOTOR_3.13, MOTOR_3.24, MOTOR_3.SLUG1, MOTOR_5.13, MOTOR_5.24, MOTOR_5.SLUG1, P5.1, U$3.P$1
BATTERY-VOLTAGE(ANALOG): R19.2, R20.1
BDOWN: DOWN.3, DOWN.4, R22.2
BSELECT: R23.2, SELECT.3, SELECT.4
BUP: R21.2, UP.3, UP.4
COMS-CS: TEENSY.31, TEENSY1.31
COMS-MISO: TEENSY.1, TEENSY1.1
COMS-MOSI: TEENSY.0, TEENSY1.0
COMS-SCK: TEENSY.32, TEENSY1.32
GND: BLUETOOTH.3, C1.1, C2.1, C3.1, C4.1, C5.1, C6.1, C7.1, C8.1, C9.1, C10.1, C11.1, C12.1, C13.1, C14.1, C15.1, C16.1, C17.1, C18.1, C19.1, C20.1, C21.1, C22.1, C23.1, C24.1, C25.-, C27.-, C29.-, C31.-, C33.-, C34.2, C48.2, C49.2, C50.2, C51.1, C52.2, C53.2, C54.2, C55.2, CN1.2, IMU.2, J1.1, MOTOR_1.1, MOTOR_1.3, MOTOR_1.4, MOTOR_1.5, MOTOR_1.6, MOTOR_1.7, MOTOR_1.30, MOTOR_1.31, MOTOR_1.32, MOTOR_1.33, MOTOR_1.34, MOTOR_1.36, MOTOR_2.1, MOTOR_2.3, MOTOR_2.4, MOTOR_2.5, MOTOR_2.6, MOTOR_2.7, MOTOR_2.30, MOTOR_2.31, MOTOR_2.32, MOTOR_2.33, MOTOR_2.34, MOTOR_2.36, MOTOR_3.1, MOTOR_3.3, MOTOR_3.4, MOTOR_3.5, MOTOR_3.6, MOTOR_3.7, MOTOR_3.30, MOTOR_3.31, MOTOR_3.32, MOTOR_3.33, MOTOR_3.34, MOTOR_3.36, MOTOR_5.1, MOTOR_5.3, MOTOR_5.4, MOTOR_5.5, MOTOR_5.6, MOTOR_5.7, MOTOR_5.30, MOTOR_5.31, MOTOR_5.32, MOTOR_5.33, MOTOR_5.34, MOTOR_5.36, OPEN-MV.28, P5.2, P5.4, R10.1, R15.1, R20.2, R21.1, R22.1, R23.1, R25.1, R28.1, SCREEN.4, TEENSY.GND, TEENSY.GND-1, TEENSY.GND-2, TEENSY.GND-3, TEENSY.GND-4, TEENSY1.GND, TEENSY1.GND-1, TEENSY1.GND-2, TEENSY1.GND-3, TEENSY1.GND-4, TSSP1.2, TSSP2.2, TSSP3.2, TSSP4.2, TSSP5.2, TSSP6.2, TSSP7.2, TSSP8.2, TSSP9.2, TSSP10.2, TSSP11.2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
MOTOR-BL(PWM): R27.1, R28.2
MOTOR-BR(PWM): R14.1, R15.2
MOTOR-FL(PWM): R9.1, R10.2
MOTOR-FR(PWM): R24.1, R25.2
unnamed: J1.2, U$2.5, U$2.6, U$2.7, U$2.8
unnamed: MOTOR_FUSE.P$2, U$3.P$2
unnamed: C25.+, LOGIC_FUSE.P$1, MOTOR_FUSE.P$1, R19.1, U$2.1, U$2.2, U$2.3
unnamed: LOGIC_FUSE.P$2, U$1.P$1
unnamed: MOTOR_1.15, R7.2
unnamed: MOTOR_5.15, R5.2
unnamed: MOTOR_5.17, R24.2
unnamed: MOTOR_5.22, R6.2
unnamed: C26.1, MOTOR_5.2, MOTOR_5.8, MOTOR_5.9, MOTOR_5.10, MOTOR_5.11, MOTOR_5.12, MOTOR_5.14, MOTOR_5.SLUG2, P1.2
unnamed: MOTOR_1.22, R8.2
unnamed: MOTOR_5.19, MOTOR_5.20
unnamed: C26.2, MOTOR_5.23, MOTOR_5.25, MOTOR_5.26, MOTOR_5.27, MOTOR_5.28, MOTOR_5.29, MOTOR_5.35, MOTOR_5.SLUG3, P1.1
unnamed: MOTOR_1.17, R9.2
unnamed: MOTOR_1.19, MOTOR_1.20
unnamed: C28.2, MOTOR_1.23, MOTOR_1.25, MOTOR_1.26, MOTOR_1.27, MOTOR_1.28, MOTOR_1.29, MOTOR_1.35, MOTOR_1.SLUG3, P2.1
unnamed: C28.1, MOTOR_1.2, MOTOR_1.8, MOTOR_1.9, MOTOR_1.10, MOTOR_1.11, MOTOR_1.12, MOTOR_1.14, MOTOR_1.SLUG2, P2.2
unnamed: MOTOR_1.16, MOTOR_1.21, R11.1
unnamed: MOTOR_2.15, R12.2
unnamed: MOTOR_2.22, R13.2
unnamed: MOTOR_2.17, R14.2
unnamed: MOTOR_2.19, MOTOR_2.20
unnamed: C30.2, MOTOR_2.23, MOTOR_2.25, MOTOR_2.26, MOTOR_2.27, MOTOR_2.28, MOTOR_2.29, MOTOR_2.35, MOTOR_2.SLUG3, P3.1
unnamed: C30.1, MOTOR_2.2, MOTOR_2.8, MOTOR_2.9, MOTOR_2.10, MOTOR_2.11, MOTOR_2.12, MOTOR_2.14, MOTOR_2.SLUG2, P3.2
unnamed: MOTOR_2.16, MOTOR_2.21, R16.1
unnamed: MOTOR_3.15, R17.2
unnamed: MOTOR_3.22, R18.2
unnamed: MOTOR_3.17, R27.2
unnamed: MOTOR_3.19, MOTOR_3.20
unnamed: C32.2, MOTOR_3.23, MOTOR_3.25, MOTOR_3.26, MOTOR_3.27, MOTOR_3.28, MOTOR_3.29, MOTOR_3.35, MOTOR_3.SLUG3, P4.1
unnamed: C32.1, MOTOR_3.2, MOTOR_3.8, MOTOR_3.9, MOTOR_3.10, MOTOR_3.11, MOTOR_3.12, MOTOR_3.14, MOTOR_3.SLUG2, P4.2
unnamed: MOTOR_5.16, MOTOR_5.21, R26.1
unnamed: MOTOR_3.16, MOTOR_3.21, R29.1
unnamed: 3.3V-DIRECT.2, SCREEN.5
unnamed: 3.3V-3.3V.2, 5V-3.3V.2, SCREEN.6
unnamed: C52.1, U$1.P$2, VREG-5.1
unnamed: C54.1, D2.C, VREG-3.3.3
RX(BLUETOOTH): BLUETOOTH.5, TEENSY.10
SCL(IMU): IMU.3, R1.2, TEENSY.3
SDA(IMU): IMU.4, R2.2, TEENSY.4
TX(BLUETOOTH): BLUETOOTH.4, TEENSY.9

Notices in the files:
parts and their libraries:
SparkFun-Resistors: Licensing: Creative Commons ShareAlike 4.0 International - https://creativecommons.org/licenses/by-sa/4.0
